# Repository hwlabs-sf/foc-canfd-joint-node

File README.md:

# foc-canfd-joint-node

A 42 mm, 48 V / 15 A brushless joint controller for humanoid and legged robots: STM32G431 +
DRV8323RS + six 1.45 mΩ MOSFETs, three Kelvin-sensed low-side shunts, an on-axis 14-bit magnetic
encoder, and CAN-FD for daisy-chained limbs.

Everything in this repository is the actual design input, not a description of one: the KiCad
schematic and four-layer board, a dual-source BOM, the FOC firmware, a CAN-FD wire codec, and the
verification suite that gates all of it.

## Specification

| Parameter | Value |
| :--- | :--- |
| Supply | 24–60 V DC (48 V nominal), reverse-polarity + surge protected (`D1` SMBJ58A) |
| Phase current | 15 A continuous with the board on a 5 mm aluminium spreader |
| Power stage | 6 × `BSC014N06NS` (60 V, 1.45 mΩ) in a 3-phase bridge |
| Gate driver | `DRV8323RS`, 3 integrated current-sense amplifiers, SPI-configurable |
| Current sense | 3 × 1 mΩ 2512 Kelvin shunts (`R1`–`R3`), low-side |
| Encoder | `MA730GQ`, 14-bit on-axis magnetic, SPI |
| Host bus | CAN-FD at 5 Mbit/s (`TCAN1044VDRQ1`), 2 × JST-GH 4-pin in/out |
| Logic | 3.3 V from `TLV75533`, 5 V from `LMR36506` (65 V input) |
| Board | 42.0 mm circle, 4 layers, 1.6 mm, Ø14 mm centre bore, 4 × M2.5 on a Ø36 mm bolt circle |
| Control rate | 20 kHz centre-aligned PWM, current loop in the TIM1 ISR |

## Power and signal chain

```
48 V ──┬── D1 SMBJ58A ──┬── Q1/Q3/Q5 (high side) ── U/V/W ── J1/J2 XT30 daisy chain
       │                │
       └── U5 LMR36506 ─┴── 5 V ── U6 TLV75533 ── 3.3 V ── U1 STM32G431
                                 │                        │
                                 └── U4 TCAN1044 ── CANH/CANL ── J3/J4 JST-GH
Q2/Q4/Q6 (low side) ── R1/R2/R3 (1 mΩ Kelvin) ── SOA/SOB/SOC ── U2 DRV8323RS
```

The sense resistors sit on the low side so the DRV8323RS amplifiers see a ground-referenced signal
without a high-voltage common mode. Each shunt has four pads: two carry the phase current, two tap the
inner edge of the element for the Kelvin connection.

## Firmware

`firmware/foc_control.c` — Clarke, Park, inverse Park, min-max-injection SVPWM with a circular
over-modulation limiter, two PI current regulators with clamping anti-windup, and the MIT Mini-Cheetah
impedance law:

```
tau = kp * (p_des - p) + kd * (v_des - v) + t_ff
iq_ref = clamp(tau * derate(temp) / Kt, ±15 A)
```

`derate()` is 1.0 up to 85 °C, falls linearly to 0 at 110 °C, and hard-cuts above that.

`firmware/canfd_codec.c` — two fixed-point frames, little-endian:

| Frame | ID | Length | Layout |
| :--- | :--- | :--- | :--- |
| MIT command | `0x100 + node` | 8 B | `p_des` i16 ×1 mrad · `v_des` i16 ×0.01 rad/s · `kp` u8 ×0.5 Nm/rad · `kd` u8 ×0.01 Nm·s/rad · `t_ff` i16 ×1 mNm |
| Joint status | `0x200 + node` | 12 B | `p` i16 · `v` i16 · `iq` i16 · `id` i16 (all ×0.01 in SI) · `vbus` u16 ×0.25 V · `temp` i8 °C · `fault` u8 bitfield |

Both directions saturate at the wire limits instead of wrapping, so a garbage frame can never command
a wrapped-around current.

## Verification

```bash
# the DFM gate this board is required to pass
python github_showcase/kicad-dfm-precheck/dfm_check.py \
    --min-annular 0.15 \
    github_showcase/foc-canfd-joint-node/hardware/foc_joint.kicad_pcb \
    github_showcase/foc-canfd-joint-node/hardware/foc_joint.kicad_sch
# -> 0 error(s), 0 warning(s), exit 0

# the suite: DFM, BOM↔schematic parity, geometry, SVG, transforms, SVPWM, PI, MIT law, CAN-FD
python -m unittest discover -s github_showcase/foc-canfd-joint-node/tests -v
```

The suite compiles both translation units with `-std=c99 -Wall -Wextra -Werror` when a C compiler is on
`PATH`, and skips that single test otherwise; the remaining 36 checks run with the standard library
alone.

What it actually asserts:

- `dfm_check.py` exits 0 at a **0.15 mm** annular-ring limit — no via, no pad, and no placeholder value
  is allowed to slip through;
- every BOM row has an LCSC code and a DigiKey alternate, and the designator set matches the schematic
  1:1 in both directions;
- the outline is Ø42.0 mm with a Ø14 mm bore, four mounting holes land on a Ø36 mm bolt circle, and the
  stack-up has exactly four copper layers;
- the SVG parses and carries the geometry it claims to;
- Clarke preserves amplitude, Park round-trips, SVPWM keeps `max + min = 1` inside the linear circle and
  clamps outside it, the MIT law is linear in position and velocity, derating crosses zero at 110 °C;
- the CAN-FD frames match the documented byte layout exactly, including saturation.

## Bill of materials

`hardware/BOM.csv` is one row per designator with manufacturer, MPN, a real LCSC `Cxxxxx` code, and a
DigiKey alternate MPN. The LCSC column is queried against JLCPCB's assembly library, so the codes are
the ones an assembler will actually match on.

## Known limitations (rev A)

- No brake chopper: regeneration into a full 48 V pack has to be absorbed by the supply or limited in
  firmware. Rev B is planned with a dump resistor and comparator.
- The DRV8323RS internal amplifiers are used; an external INA240 front end would give better common-mode
  rejection above 40 A.
- The CAN-FD termination resistor (`R9`, 120 Ω) is populated on both `J3` and `J4` in the current BOM
  layout; on a long daisy chain, fit it only at the two physical ends.
- Thermal numbers assume a spreader; free-air operation is limited by the FET case rise, not by the
  shunts.

## Licence

MIT — see `LICENSE`. Design files, firmware and tests are all covered by the same terms.

HW Labs / Hengwu Engineering — <https://hengwu.online/labs>

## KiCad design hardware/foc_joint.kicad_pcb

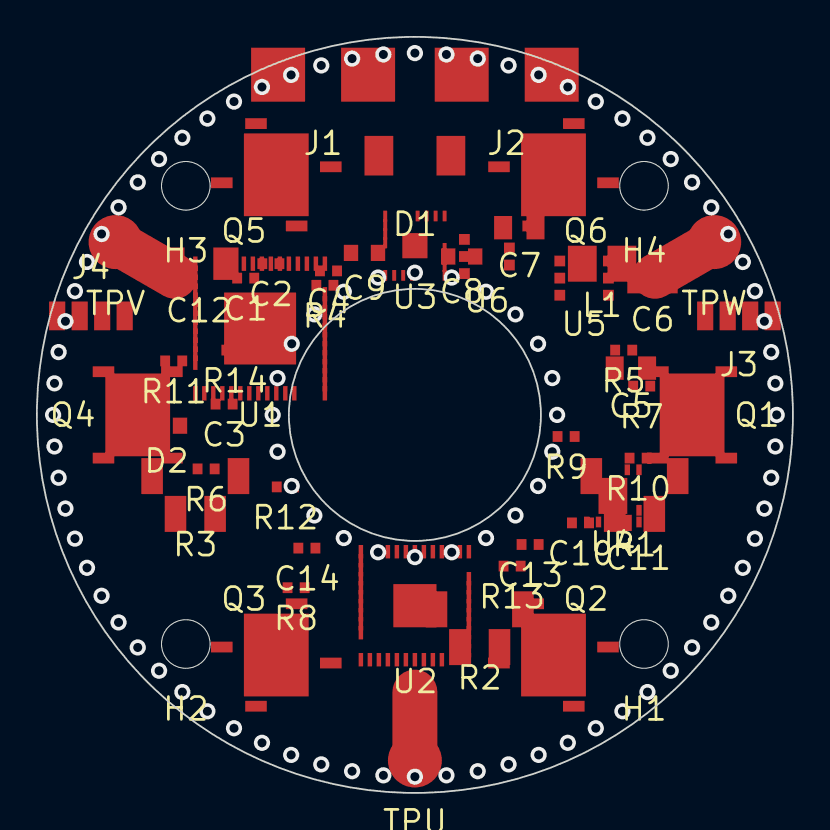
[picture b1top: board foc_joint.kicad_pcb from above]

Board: 4 copper layers, 42.0 x 42.0 mm, 54 parts (0 on the bottom side), 26 nets.

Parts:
C1, C2, C3, C4: 100nF 16V X7R; 0402
C5, C7: 10uF 10V X5R; 0805
C6: 22uF 10V X5R; 0805
C8, C9: 1uF 16V X5R; 0603
C10, C13, C14: 100nF 50V X7R; 0402
C11: 4.7uF 16V X5R; 0603
C12: 47uF 63V; 1206
D1: SMBJ58A; SMB
D2: LED green 0603; 0603
H1, H2, H3, H4: M2.5; MountingHole_2.7mm_M2.5
J1: XT30UPB-M; XT30
J2: XT30UPB-F; XT30
J3: JST-GH-4P CAN IN; GH-4
J4: JST-GH-4P CAN OUT; GH-4
L1: 4.7uH 2.1A; 4020
Q1, Q2, Q3, Q4, Q5, Q6: BSC014N06NS; SuperSO8
R1, R2, R3: 1mR 1% 2W; 2512
R4, R5, R7, R8, R10: 10k 1%; 0402
R6: 100R 1%; 0402
R9: 120R 1%; 0402
R11, R14: 1k 1%; 0402
R12, R13: 100k 1%; 0402
TPU: PHASE_A; Pad_Phase_3.0
TPV: PHASE_B; Pad_Phase_3.0
TPW: PHASE_C; Pad_Phase_3.0
U1: STM32G431CBU6; UFQFPN-48
U2: DRV8323RS; VQFN-40
U3: MA730GQ; QFN-16
U4: TCAN1044VDRQ1; SON-8
U5: LMR36506MSC5RPERQ1; SOT-23-6
U6: TLV75533PDBVR; SOT-23-5

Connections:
+3V3: C1.1, C2.1, C3.1, C4.1, C5.1, C6.1, C7.1, C8.1, C9.1, C10.1, C11.1, C12.1, C13.1, C14.1, R4.1, R5.1, R6.1, R7.1, R8.1, R9.1, R10.1, R11.1, R12.1, R13.1, R14.1, U1.1, U1.48, U2.16, U3.1, U6.4
+5V: J3.1, J4.1, L1.2, U2.15, U4.1, U4.8, U5.6, U6.1
+48V: D1.1, J1.1, J2.1, Q1.1, Q3.1, Q5.1, U2.1, U2.26, U5.1
CANH: J3.2, J4.2, U4.5
CANL: J3.3, J4.3, U4.6
GH_A: Q1.3, U2.3
GH_B: Q3.3, U2.4
GH_C: Q5.3, U2.5
GL_A: Q2.3, U2.6
GL_B: Q4.3, U2.7
GL_C: Q6.3, U2.8
GND: C1.2, C2.2, C3.2, C4.2, C5.2, C6.2, C7.2, C8.2, C9.2, C10.2, C11.2, C12.2, C13.2, C14.2, D1.2, J1.2, J2.2, J3.4, J4.4, Q1.EP, Q2.2, Q2.EP, Q3.EP, Q4.2, Q4.EP, Q5.EP, Q6.2, Q6.EP, R1.2, R1.4, R2.2, R2.4, R3.2, R3.4, R4.2, R5.2, R6.2, R7.2, R8.2, R9.2, R10.2, R11.2, R12.2, R13.2, R14.2, U1.2, U1.EP, U2.2, U2.24, U2.25, U2.27, U2.31, U2.32, U2.33, U2.34, U2.35, U2.36, U2.37, U2.38, U2.39, U2.40, U2.EP, U3.2, U3.9, U3.10, U3.11, U3.12, U3.13, U3.14, U3.15, U3.16, U3.EP, U4.2, U4.7, U4.EP, U5.2, U6.2, U6.5
LED_K: D2.1, D2.2
PHASE_A: Q1.2, Q2.1, TPU.1, U2.28
PHASE_B: Q3.2, Q4.1, TPV.1, U2.29
PHASE_C: Q5.2, Q6.1, TPW.1, U2.30
SH_A: Q1.4, Q2.4, R1.1, U2.9
SH_B: Q3.4, Q4.4, R2.1, U2.10
SH_C: Q5.4, Q6.4, R3.1, U2.11
SOA: R1.3, U2.12
SOB: R2.3, U2.13
SOC: R3.3, U2.14
SPI_MISO: U2.21, U3.4
SPI_MOSI: U2.20, U3.5
SPI_SCK: U2.19, U3.3
SW_5V: L1.1, U5.3

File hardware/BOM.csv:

Ref,Qty,Value,Package,Manufacturer,MPN,LCSC,Alt_MPN,Alt_Distributor,Notes
U1,1,STM32G431CBU6,UFQFPN-48,STMicroelectronics,STM32G431CBU6,C529356,STM32G431CBU6,DigiKey,
U2,1,DRV8323RS,VQFN-40,Texas Instruments,DRV8323RSRGZR,C545497,DRV8323RSRGZT,DigiKey,
U3,1,MA730GQ,QFN-16,Monolithic Power Systems,MA730GQ-Z,C161798,MA730GQ,DigiKey,
U4,1,TCAN1044VDRQ1,SON-8,Texas Instruments,TCAN1044VDRBRQ1,C1852061,TCAN1044AVDRQ1,DigiKey,
U5,1,LMR36506MSC5RPERQ1,SOT-23-6,Texas Instruments,LMR36506MSC5RPERQ1,C2866484,LMR36506R5RPER,DigiKey,
U6,1,TLV75533PDBVR,SOT-23-5,Texas Instruments,TLV75533PDBVR,C404027,TLV75533PDQNR,DigiKey,
Q1,1,BSC014N06NS,SuperSO8,Infineon,BSC014N06NS,C113391,BSC014N06NSTATMA1,DigiKey,
Q2,1,BSC014N06NS,SuperSO8,Infineon,BSC014N06NS,C113391,BSC014N06NSTATMA1,DigiKey,
Q3,1,BSC014N06NS,SuperSO8,Infineon,BSC014N06NS,C113391,BSC014N06NSTATMA1,DigiKey,
Q4,1,BSC014N06NS,SuperSO8,Infineon,BSC014N06NS,C113391,BSC014N06NSTATMA1,DigiKey,
Q5,1,BSC014N06NS,SuperSO8,Infineon,BSC014N06NS,C113391,BSC014N06NSTATMA1,DigiKey,
Q6,1,BSC014N06NS,SuperSO8,Infineon,BSC014N06NS,C113391,BSC014N06NSTATMA1,DigiKey,
R1,1,1mR 1% 2W,2512,Vishay,WSL25121L000FEA18,C149567,LR2512-22R001F4,DigiKey,
R2,1,1mR 1% 2W,2512,Vishay,WSL25121L000FEA18,C149567,LR2512-22R001F4,DigiKey,
R3,1,1mR 1% 2W,2512,Vishay,WSL25121L000FEA18,C149567,LR2512-22R001F4,DigiKey,
D1,1,SMBJ58A,SMB,Diodes Inc,SMBJ58A-13-F,C135085,SMBJ58A,DigiKey,
J1,1,XT30UPB-M,XT30,AMASS,XT30UPB-M,C99101,XT30U-M,DigiKey,
J2,1,XT30UPB-F,XT30,AMASS,XT30UPB-F,C108769,XT30U-F,DigiKey,
J3,1,JST-GH-4P CAN IN,GH-4,JST,SM04B-GHS-TB(LF)(SN),C189895,SM04B-GHS-TB,DigiKey,
J4,1,JST-GH-4P CAN OUT,GH-4,JST,SM04B-GHS-TB(LF)(SN),C189895,SM04B-GHS-TB,DigiKey,
L1,1,4.7uH 2.1A,4020,Murata,DFE252012F-4R7M,C1034,SDFL1608Q4R7KTF,DigiKey,
C1,1,100nF 16V X7R,0402,Samsung,CL05B104KO5NNNC,C1525,0402B104K160NT,DigiKey,
C2,1,100nF 16V X7R,0402,Samsung,CL05B104KO5NNNC,C1525,0402B104K160NT,DigiKey,
C3,1,100nF 16V X7R,0402,Samsung,CL05B104KO5NNNC,C1525,0402B104K160NT,DigiKey,
C4,1,100nF 16V X7R,0402,Samsung,CL05B104KO5NNNC,C1525,0402B104K160NT,DigiKey,
C5,1,10uF 10V X5R,0805,Samsung,CL21A106KAYNNNE,C15850,CL21A106KOQNNNE,DigiKey,
C6,1,22uF 10V X5R,0805,Samsung,CL21A226MQQNNNE,C5674,CL21A226MPQNNNE,DigiKey,
C7,1,10uF 10V X5R,0805,Samsung,CL21A106KAYNNNE,C15850,CL21A106KOQNNNE,DigiKey,
C8,1,1uF 16V X5R,0603,Samsung,CL10A105KO8NNNC,C1592,CL10A105KA8NNNC,DigiKey,
C9,1,1uF 16V X5R,0603,Samsung,CL10A105KO8NNNC,C1592,CL10A105KA8NNNC,DigiKey,
C10,1,100nF 50V X7R,0402,Samsung,CL05B104KO5NNNC,C1525,0402B104K160NT,DigiKey,
C11,1,4.7uF 16V X5R,0603,Samsung,CL10A475KO8NNNC,C19666,CL10A475KA8NNNC,DigiKey,
C12,1,47uF 63V,1206,Panasonic,EEEFK1J470P,C160404,EEEFK1J470P,DigiKey,
C13,1,100nF 50V X7R,0402,Samsung,CL05B104KO5NNNC,C1525,0402B104K160NT,DigiKey,
C14,1,100nF 50V X7R,0402,Samsung,CL05B104KO5NNNC,C1525,0402B104K160NT,DigiKey,
R4,1,10k 1%,0402,Yageo,RC0402FR-0710KL,C25744,0402WGF1002TCE,DigiKey,
R5,1,10k 1%,0402,Yageo,RC0402FR-0710KL,C25744,0402WGF1002TCE,DigiKey,
R6,1,100R 1%,0402,Yageo,RC0402FR-07100RL,C25018,0402WGF1000TCE,DigiKey,
R7,1,10k 1%,0402,Yageo,RC0402FR-0710KL,C25744,0402WGF1002TCE,DigiKey,
R8,1,10k 1%,0402,Yageo,RC0402FR-0710KL,C25744,0402WGF1002TCE,DigiKey,
R9,1,120R 1%,0402,Yageo,RC0402FR-07120RL,C25048,0402WGF1200TCE,DigiKey,
R10,1,10k 1%,0402,Yageo,RC0402FR-0710KL,C25744,0402WGF1002TCE,DigiKey,
R11,1,1k 1%,0402,Yageo,RC0402FR-071KL,C25013,0402WGF1001TCE,DigiKey,
R12,1,100k 1%,0402,Yageo,RC0402FR-07100KL,C25021,0402WGF1003TCE,DigiKey,
R13,1,100k 1%,0402,Yageo,RC0402FR-07100KL,C25021,0402WGF1003TCE,DigiKey,
R14,1,1k 1%,0402,Yageo,RC0402FR-071KL,C25013,0402WGF1001TCE,DigiKey,
D2,1,LED green 0603,0603,Kingbright,APT1608SGC,C12417,APT1608SGC,DigiKey,
